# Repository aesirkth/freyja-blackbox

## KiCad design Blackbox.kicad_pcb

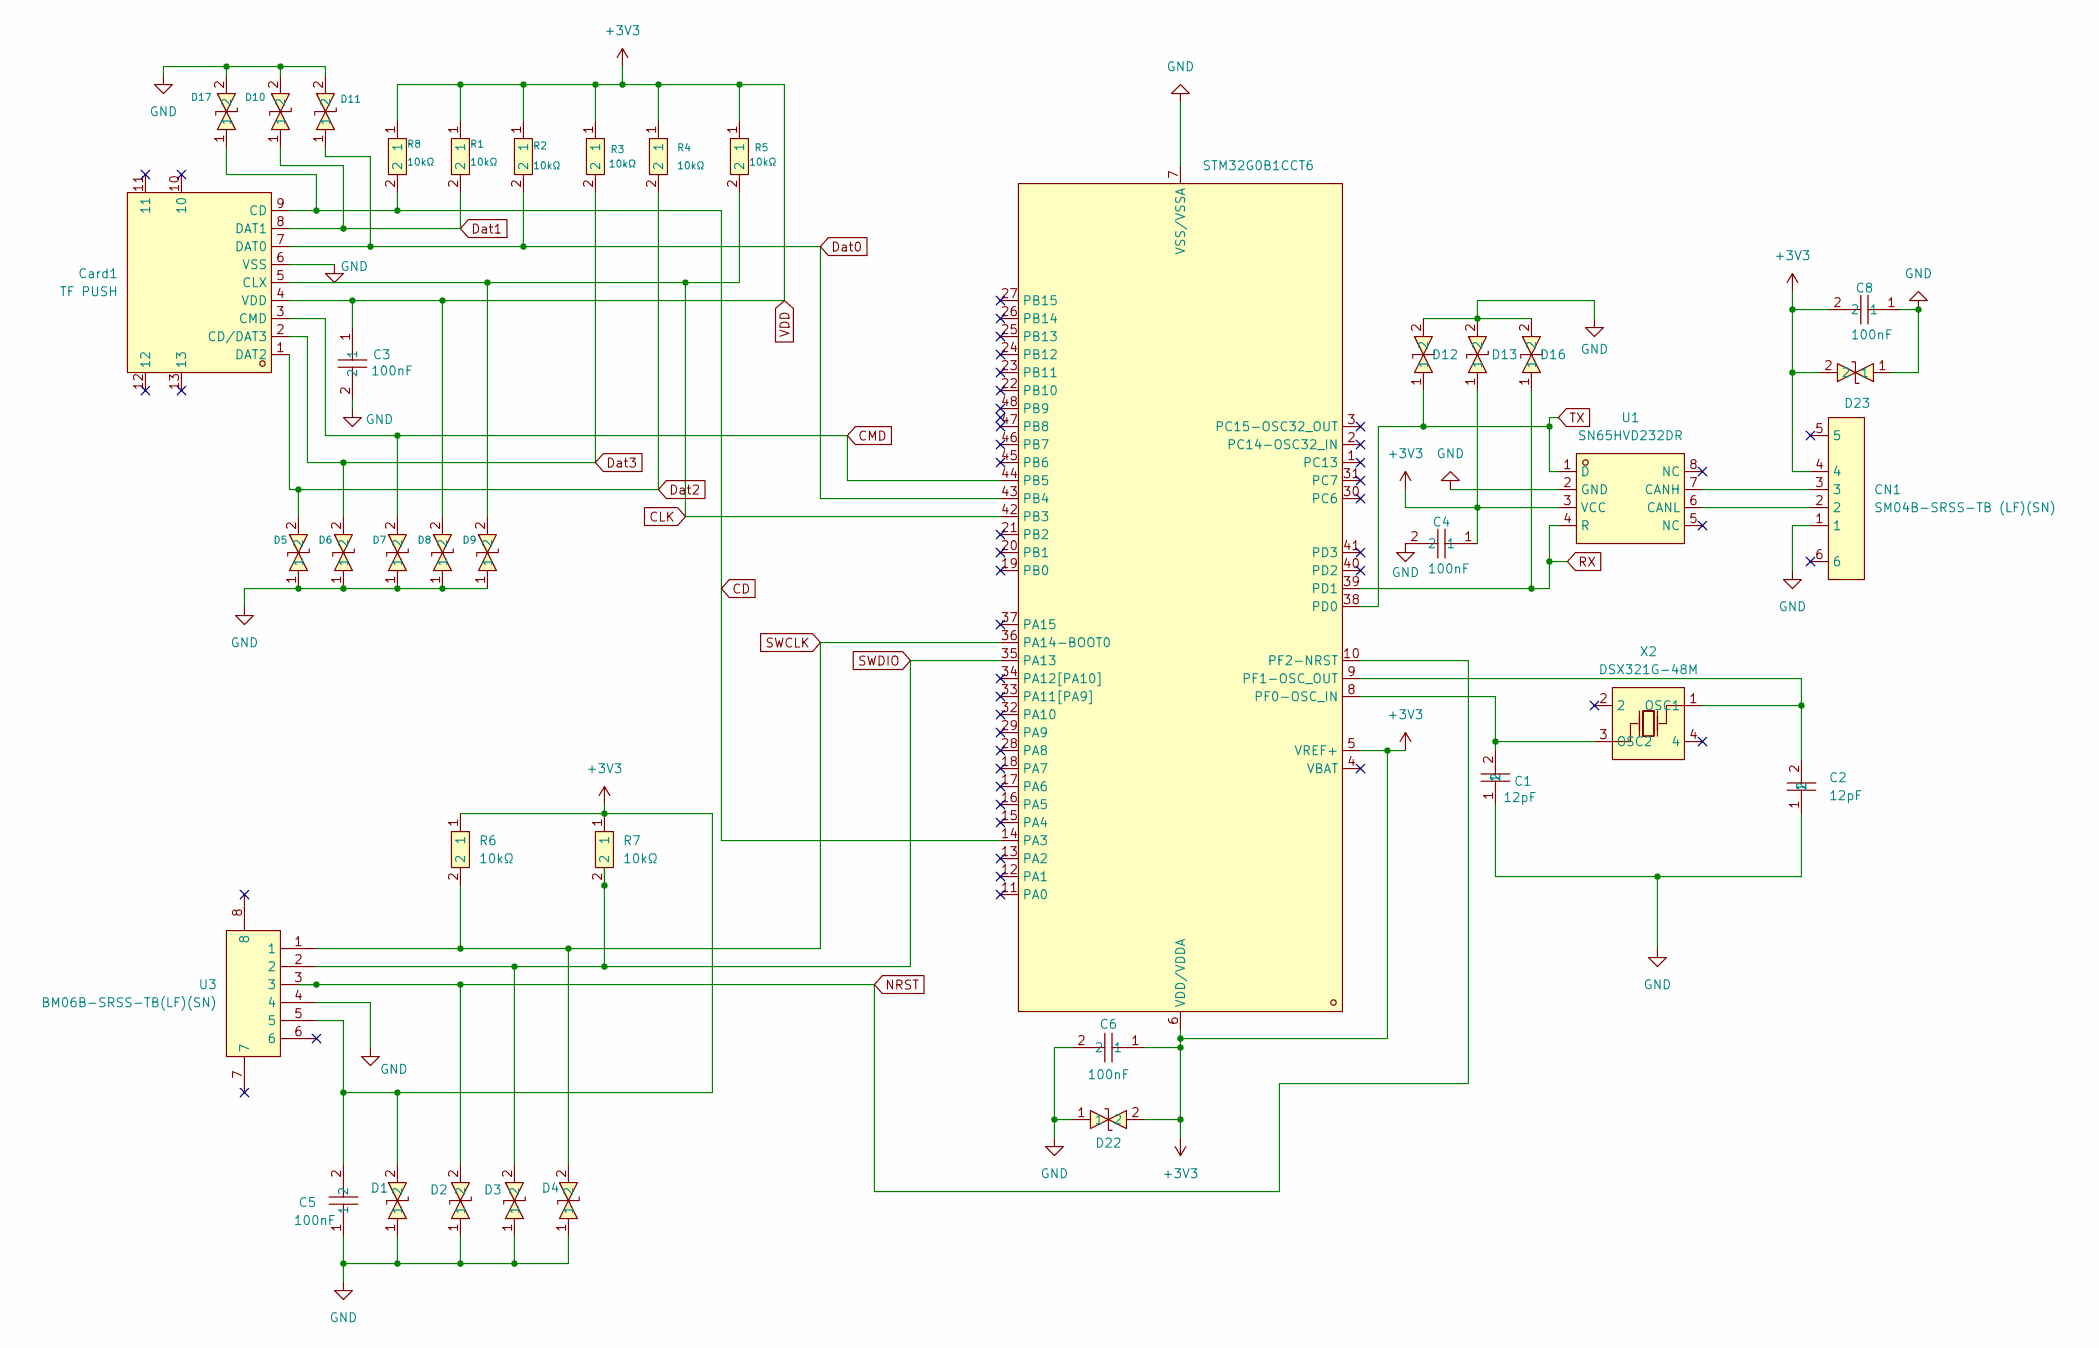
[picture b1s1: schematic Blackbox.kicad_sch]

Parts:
C1, C2: 12pF; C0402; LCSC Part C1547
C3, C4, C5, C6, C8: 100nF; C0603; LCSC Part C14663
CN1: SM04B-SRSS-TB (LF)(SN); CONN-SMD_4P-P1.00_SM04B-SRSS-TB-LF-SN; LCSC Part C160404
Card1: TF PUSH; TF-SMD_TF-PUSH; LCSC Part C393941
D1, D2, D3, D4, D5, D6, D7, D8, D9, D10, D11, D12, D13, D16, D17, D22, D23: 0603ESDA-05N; D0603-BI; LCSC Part C316054
R1, R2, R3, R4, R5, R6, R7, R8: 10kΩ; R0603; LCSC Part C2930027
U1: SN65HVD232DR; SOIC-8_L5.0-W4.0-P1.27-LS6.0-BL; LCSC Part C30530
U2: STM32G0B1CCT6; LQFP-48_L7.0-W7.0-P0.50-LS9.0-BL_1; LCSC Part C5270241
U3: BM06B-SRSS-TB(LF)(SN); CONN-SMD-6P-P1.00_BM06B-SRSS-TB-LF-SN; LCSC Part C160392
X2: DSX321G-48M; CRYSTAL-SMD_4P-L3.2-W2.5-BL; LCSC Part C127497

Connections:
CD: Card1.9 (CD), D17.1, R8.2, U2.14 (PA3)
CLK: Card1.5 (CLX), D9.2, R5.2, U2.42 (PB3)
CMD: Card1.3 (CMD), D7.2, U2.44 (PB5)
Dat0: Card1.7 (DAT0), D11.1, R2.2, U2.43 (PB4)
Dat1: Card1.8 (DAT1), D10.1, R1.2
Dat2: Card1.1 (DAT2), D5.2, R4.2
Dat3: Card1.2 (CD/DAT3), D6.2, R3.2
GND: C1.1, C2.1, C3.2, C4.2, C5.1, C6.2, C8.1, CN1.1, Card1.6 (VSS), D1.1, D2.1, D3.1, D4.1, D5.1, D6.1, D7.1, D8.1, D9.1, D10.2, D11.2, D12.2, D13.2, D16.2, D17.2, D22.1, D23.1, U1.2 (GND), U2.7 (VSS/VSSA), U3.4
NRST: D2.2, U2.10 (PF2-NRST), U3.3
unnamed: CN1.3, U1.7 (CANH)
unnamed: CN1.2, U1.6 (CANL)
unnamed: C1.2, U2.8 (PF0-OSC_IN), X2.3 (OSC2)
unnamed: C2.2, U2.9 (PF1-OSC_OUT), X2.1 (OSC1)
RX: D16.1, U1.4 (R), U2.39 (PD1)
SWCLK: D4.2, R6.2, U2.36 (PA14-BOOT0), U3.1
SWDIO: D3.2, R7.2, U2.35 (PA13), U3.2
TX: D12.1, U1.1 (D), U2.38 (PD0)
VDD: C3.1, C4.1, C5.2, C6.1, C8.2, CN1.4, Card1.4 (VDD), D1.2, D8.2, D13.1, D22.2, D23.2, R1.1, R2.1, R3.1, R4.1, R5.1, R6.1, R7.1, R8.1, U1.3 (VCC), U2.5 (VREF+), U2.6 (VDD/VDDA), U3.5

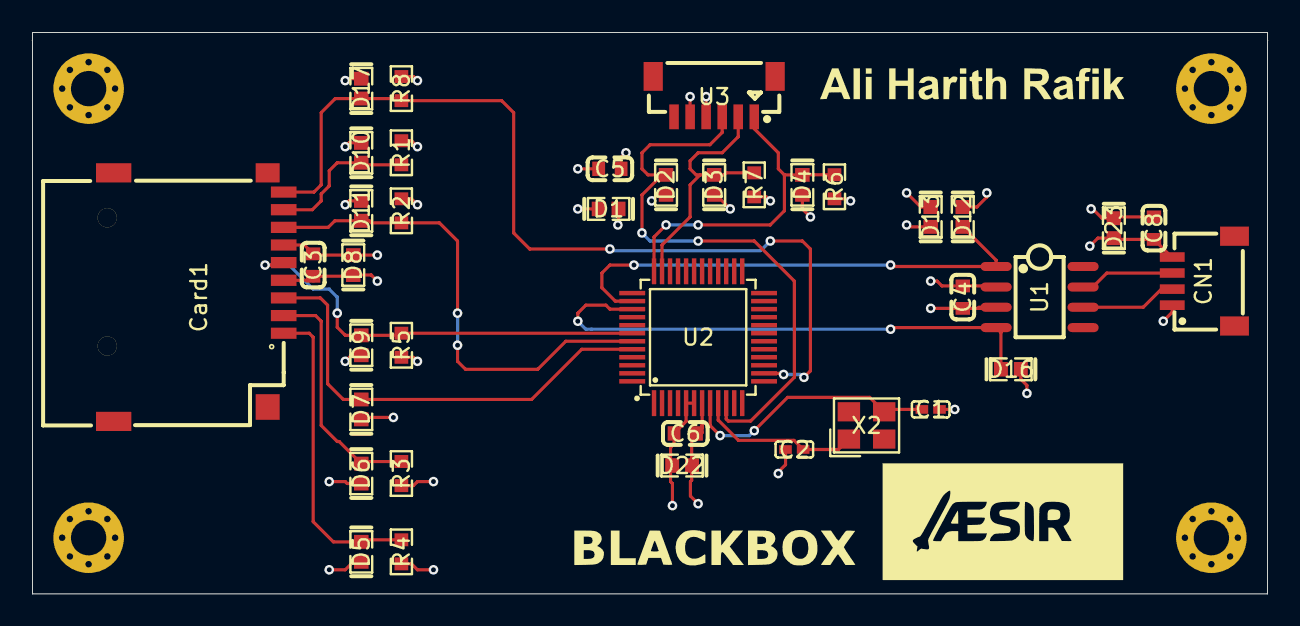
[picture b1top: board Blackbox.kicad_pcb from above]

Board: 4 copper layers, 77.0 x 35.0 mm, 38 parts (0 on the bottom side), 18 nets.

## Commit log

2025-09-17 Add PCB schematic PDF
2025-09-20 Update schematic and PCB with latest changes
2025-09-20 The PCB connections are completed
2025-09-23 updated pcb
2025-09-24 Updated pcb, only mountung holes left
2025-09-24 new pcb design
2025-09-24 PCB update
2025-09-24 Final PCB Design
2025-09-25 Final Version of the BlackBox PCB
2025-09-25 Final PCB design of the BlackBox
2025-09-25 BlackBox PCB For Freyja Rocket
2025-09-25 Version 1.0 PCB BlackBox
